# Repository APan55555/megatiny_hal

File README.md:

# megatiny_hal

Crate containing the hardware abstraction layers for attiny and atmega avr microcontrollers

## Contains support for

- attiny412

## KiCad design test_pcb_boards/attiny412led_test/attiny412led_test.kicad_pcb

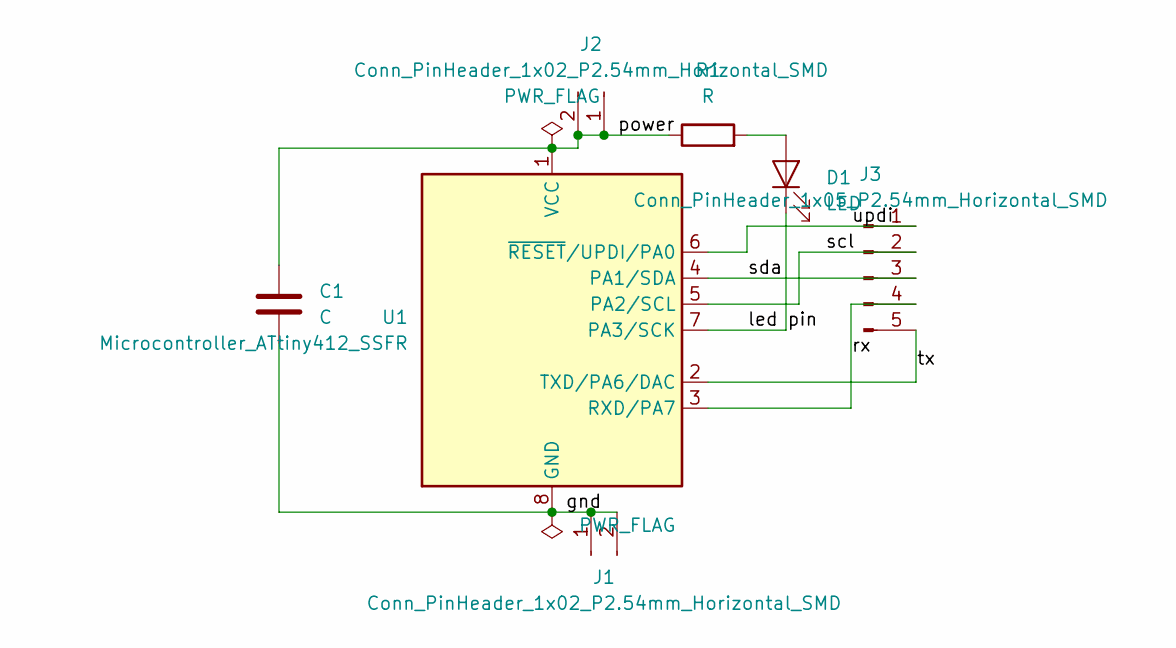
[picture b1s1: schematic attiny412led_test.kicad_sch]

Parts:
C1: C; C_1206
D1: LED; LED_1206
J1, J2: Conn_PinHeader_1x02_P2.54mm_Horizontal_SMD; PinHeader_UPDI_01x02_P2.54mm_Horizontal_SMD
J3: Conn_PinHeader_1x05_P2.54mm_Horizontal_SMD; PinHeader_1x05_P2.54mm_Horizontal_SMD
R1: R; R_1206
U1: Microcontroller_ATtiny412_SSFR; SOIC-8_3.9x4.9mm_P1.27mm

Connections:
/gnd: C1.2, J1.1, J1.2, U1.8 (GND)
/led pin: D1.1 (K), U1.7 (PA3/SCK)
/power: C1.1, J2.1, J2.2, R1.1, U1.1 (VCC)
/rx: J3.4, U1.3 (RXD/PA7)
/scl: J3.2, U1.5 (PA2/SCL)
/sda: J3.3, U1.4 (PA1/SDA)
/tx: J3.5, U1.2 (TXD/PA6/DAC)
/updi: J3.1, U1.6 (~RESET/UPDI/PA0)
unnamed: D1.2 (A), R1.2

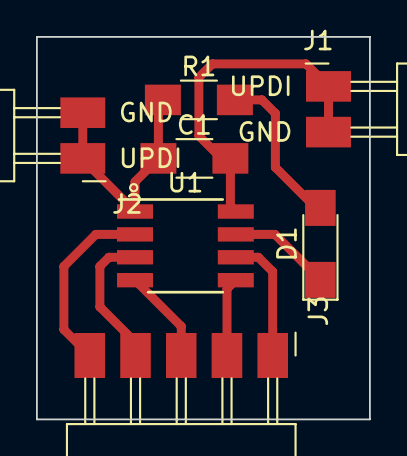
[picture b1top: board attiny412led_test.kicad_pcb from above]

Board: 2 copper layers, 18.5 x 21.2 mm, 7 parts (0 on the bottom side), 9 nets.

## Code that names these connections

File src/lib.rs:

//! Crate containing the hardware abstraction layers for attiny and atmega avr microcontrollers
//! 
//! # Contains support for
//! 
//! - attiny412

#![no_std]
#![feature(lang_items)]

pub mod attiny412pac;
pub mod attiny412;

#[lang = "eh_personality"]
extern "C" fn eh_personality() {}

/// Returns a Pin enum with input formatted (\[peripherals\], \[pin number formatted \[port\]\[pin number\]\] input/output)
/// 
/// # Examples
/// 
/// ```
/// let periphs = get_periphs();
/// let led_pin = Pin!(periphs, PA3 output);
/// ```
/// 
/// ```
/// let periphs = get_periphs();
/// let button_pin = Pin!(periphs, PA1 input);
/// ```
#[macro_export]
macro_rules! Pin {
    ($p:expr, PA0 output) => {
        {
            let porta = $p.PORTA.deref();
            porta.dirset.write(|w| unsafe { w.bits(0b1) });
            Pin::new($p, PinSelect::PA0)
        }
    };
    ($p:expr, PA0 input) => {
        {
            let porta = $p.PORTA.deref();
            porta.dirclr.write(|w| unsafe { w.bits(0b1) });
            Pin::new($p, PinSelect::PA0)
        }
    };
    ($p:expr, PA1 output) => {
        {
            let porta = $p.PORTA.deref();
            porta.dirset.write(|w| unsafe { w.bits(0b1 << 1) });
            Pin::new($p, PinSelect::PA1)
        }
    };
    ($p:expr, PA1 input) => {
        {
            let porta = $p.PORTA.deref();
            porta.dirclr.write(|w| unsafe { w.bits(0b1 << 1) });
            Pin::new($p, PinSelect::PA1)
        }
    };
    ($p:expr, PA2 output) => {
        {
            let porta = $p.PORTA.deref();
            porta.dirset.write(|w| unsafe { w.bits(0b1 << 2) });
            Pin::new($p, PinSelect::PA2)
        }
    };
    ($p:expr, PA2 input) => {
        {
            let porta = $p.PORTA.deref();
            porta.dirclr.write(|w| unsafe { w.bits(0b1 << 2) });
            Pin::new($p, PinSelect::PA2)
        }
    };
    ($p:expr, PA3 output) => {
        {
            let porta = $p.PORTA.deref();
            porta.dirset.write(|w| unsafe { w.bits(0b1 << 3) });
            Pin::new($p, PinSelect::PA3)
        }
    };
    ($p:expr, PA3 input) => {
        {
            let porta = $p.PORTA.deref();
            porta.dirclr.write(|w| unsafe { w.bits(0b1 << 3) });
            Pin::new($p, PinSelect::PA3)
        }
    };
    ($p:expr, PA4 output) => {
        {
            let porta = $p.PORTA.deref();
            porta.dirset.write(|w| unsafe { w.bits(0b1 << 4) });
            Pin::new($p, PinSelect::PA4)
        }
    };
    ($p:expr, PA4 input) => {
        {
            let porta = $p.PORTA.deref();
            porta.dirclr.write(|w| unsafe { w.bits(0b1 << 4) });
            Pin::new($p, PinSelect::PA4)
        }
    };
    ($p:expr, PA5 output) => {
        {
            let porta = $p.PORTA.deref();
            porta.dirset.write(|w| unsafe { w.bits(0b1 << 5) });
            Pin::new($p, PinSelect::PA5)
        }
    };
    ($p:expr, PA5 input) => {
        {
            let porta = $p.PORTA.deref();
            porta.dirclr.write(|w| unsafe { w.bits(0b1 << 5) });
            Pin::new($p, PinSelect::PA5)
        }
    };
    ($p:expr, PA6 output) => {
        {
            let porta = $p.PORTA.deref();
            porta.dirset.write(|w| unsafe { w.bits(0b1 << 6) });
            Pin::new($p, PinSelect::PA6)
        }
    };
    ($p:expr, PA6 input) => {
        {
            let porta = $p.PORTA.deref();
            porta.dirclr.write(|w| unsafe { w.bits(0b1 << 6) });
            Pin::new($p, PinSelect::PA6)
        }
    };
    ($p:expr, PA7 output) => {
        {
            let porta = $p.PORTA.deref();
            porta.dirset.write(|w| unsafe { w.bits(0b1 << 7) });
            Pin::new($p, PinSelect::PA7)
        }
    };
    ($p:expr, PA7 input) => {
        {
            let porta = $p.PORTA.deref();
            porta.dirclr.write(|w| unsafe { w.bits(0b1 << 7) });
            Pin::new($p, PinSelect::PA7)
        }
    };
}

///A trait for GPIO pins
pub trait GPIO {
    fn write_high(&self);

    fn write_low(&self);

    fn toggle(&self);

    fn read(&self) -> bool;
}

/*
#[macro_export]
macro_rules! Interrupt {
    (attiny412, $p:expr, $i:expr, $f:expr) => {
        match $i {
            Interrupt::CRCSCAN_NMI => {
                $p.NVMCTRL.deref()
            }
        }
    }
}*/

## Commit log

2022-07-30 generated svd
2022-07-31 edited svd
2022-08-01 generated rust PAC
2022-08-02 used wrong target flag for svd2rust, fixed the issue and added dependencies
2022-08-02 ran cargo fmt
2022-08-02 ran form
2022-08-02 added custom json target file to git ignore
2022-08-02 added .cargo directory to git ignore
2022-08-03 designed test attiny led board
2022-08-03 deleted unnecessary files
2022-08-03 successfully compiled
2022-08-05 changed bin to examples
2022-08-10 added edge cuts to 412 led test
2022-08-16 Revert "edited svd"
    This reverts commit 8f88531a80ceb00dc0ea14e2f6203bdad28a0605.
2022-08-16 regenerated rust
2022-08-17 working blink code example and added back build.rs and device.x
2022-08-18 moved pac to module
2022-08-21 made hal first iteration
2022-08-21 updated lib and completed hal blink example
2022-08-21 added placeholder eh personality and removed panic abort from cargo.toml
2022-08-21 added documentation and delay microseconds
2022-08-21 restructured files and fixed lisense.md typo
2022-08-21 added cargo publish stuff
2022-08-21 added crate and module documentation and added authors and repo
2022-08-21 fixed authors field format
2022-08-21 added read me
2022-11-22 updated to version 0.2.0 with change in Pin from enum to struct and change in delay function, also added a toolchain.toml file
2022-11-22 added homepage
2022-11-22 added files to exclude from cargo publishing
2023-02-22 made everything inline always
2023-02-25 fixed attiny412 svd to includge cpu sreg register
2023-03-18 added new cpu register and bug fixes
